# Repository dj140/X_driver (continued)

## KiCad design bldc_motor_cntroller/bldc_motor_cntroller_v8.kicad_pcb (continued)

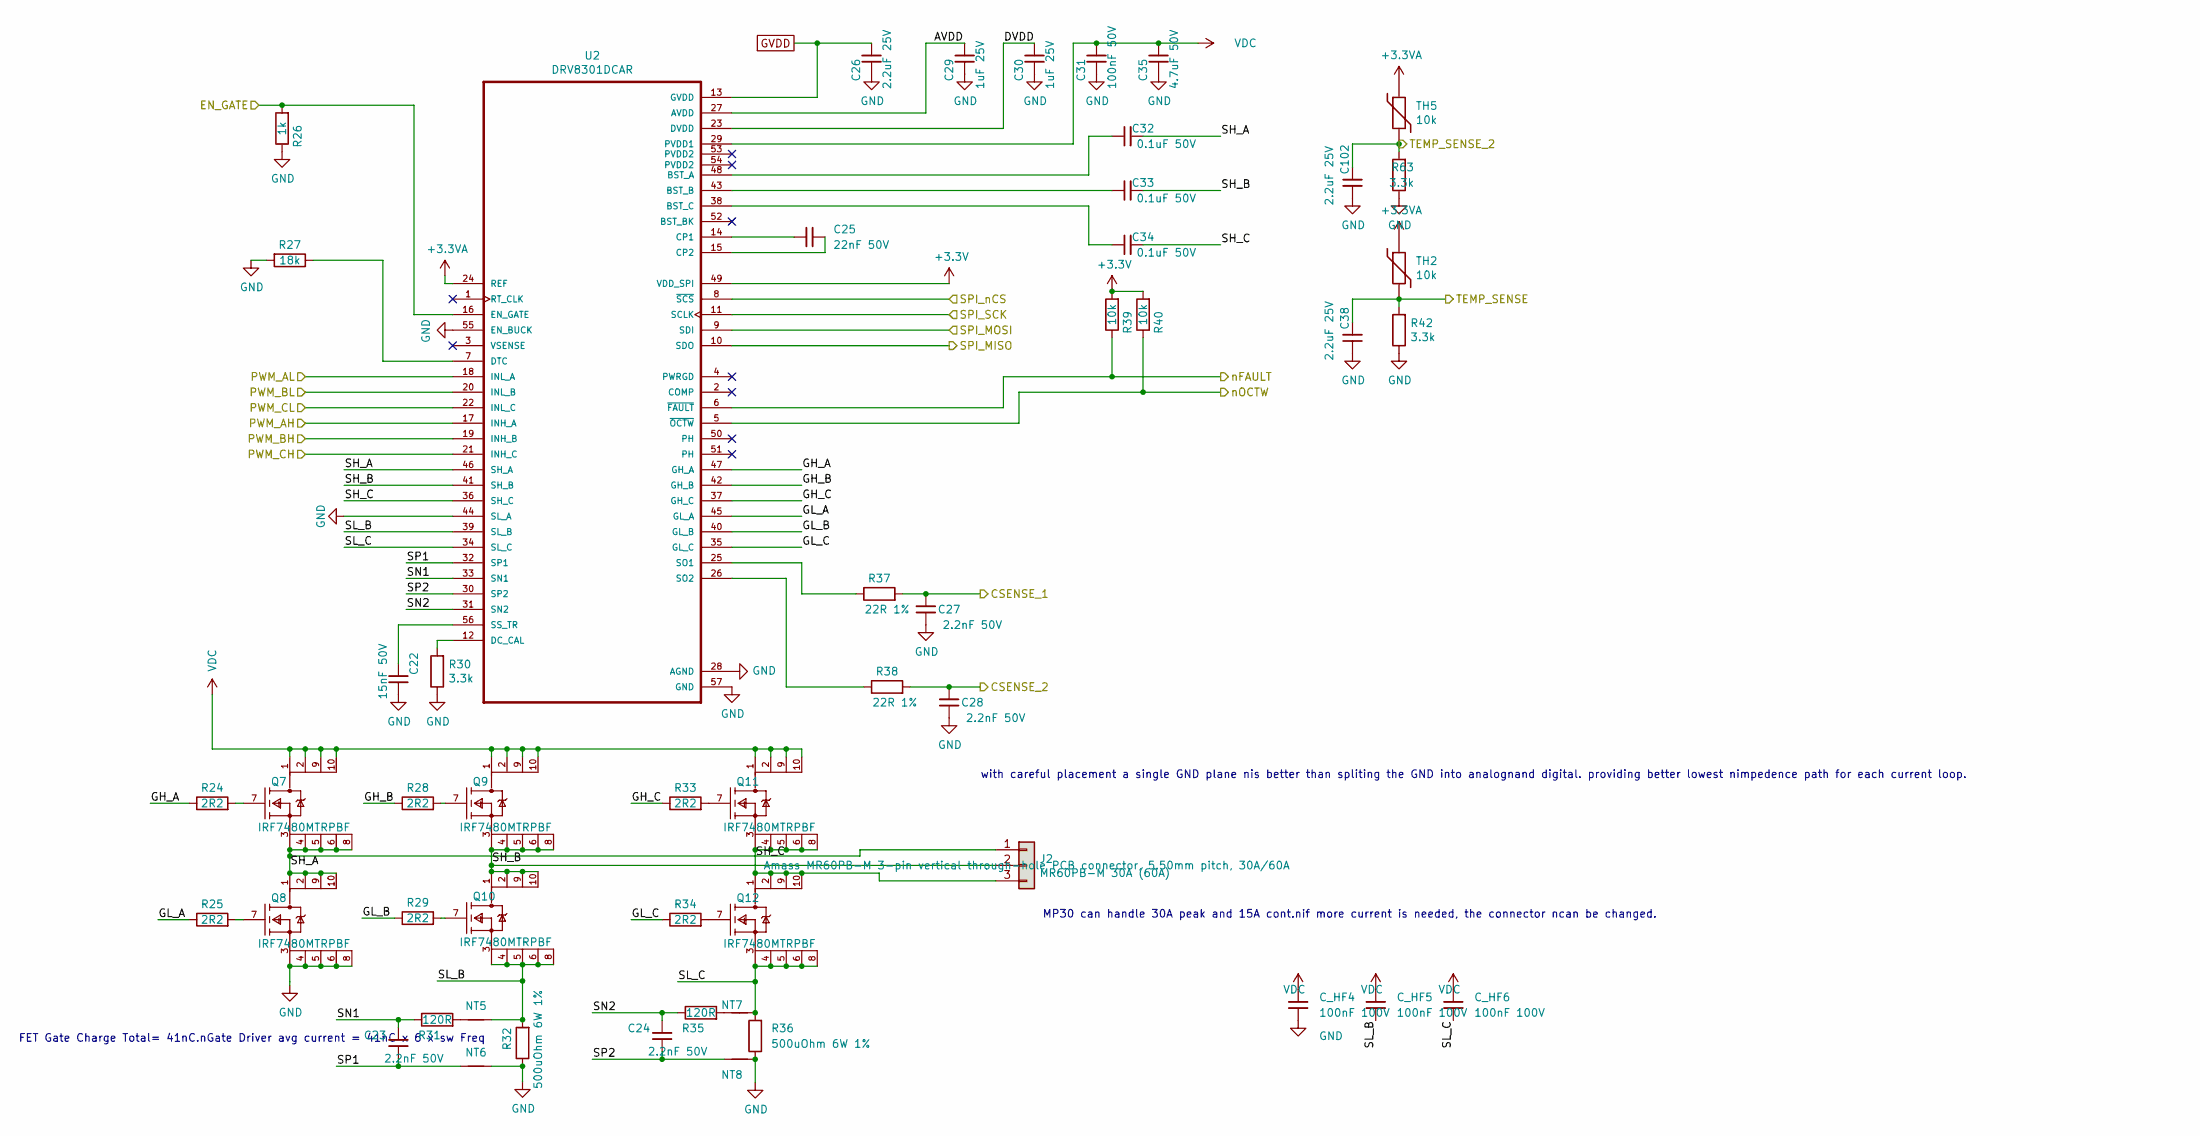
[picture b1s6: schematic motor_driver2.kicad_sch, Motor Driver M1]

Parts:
C22: 15nF 50V; C_0402_1005Metric; MPN GCM155R71E153JA55D
C23, C24, C27, C28: 2.2nF 50V; C_0402_1005Metric; MPN C0402C222J3GEC7411; LCSC Part # C1531
C25: 22nF 50V; C_0402_1005Metric; MPN C0402C223K5REC7411; LCSC Part # C1532
C26, C38, C102: 2.2uF 25V; C_0402_1005Metric; MPN GRM155C81E225KE11D; LCSC Part # C12530
C29, C30: 1uF 25V; C_0402_1005Metric; MPN GMK105CC6105MV-F; LCSC Part # C52923
C31: 100nF 50V; C_0402_1005Metric; MPN GRM155R62A104KE14D
C32, C33, C34: 0.1uF 50V; C_0402_1005Metric; MPN GCM155L8EH104KE07D
C35: 4.7uF 50V; C_1206_3216Metric; MPN HMK325C7475KN-TE
C_HF4, C_HF5, C_HF6: 100nF 100V; C_0603_1608Metric; MPN GCM188R72A104KA64D
J2: MR60PB-M 30A (60A); AMASS_MR60PB-M_1x03_P5.50mm_Vertical; MPN MR60PB-M
NT5, NT6, NT7, NT8: Net-Tie_2; NetTie-2_SMD_Pad0.5mm
Q7, Q8, Q9, Q10, Q11, Q12: IRF7480MTRPBF; Infineon-MG-WDSON-8-05_2016-901-MFG; mouser part number 942-IRF7480MTRPBF; digikey description MOSFET N-CH 40V 217A DIRECTFET
R24, R25, R28, R29, R33, R34: 2R2; R_0402_1005Metric; MPN CRCW04022R20FKEDC
R26: 1k; R_0402_1005Metric; MPN ERJ-2RKF1001X; LCSC Part # C11702
R27: 18k; R_0402_1005Metric; MPN CRCW040218K0FKED; LCSC Part # C25762
R30, R42, R63: 3.3k; R_0402_1005Metric; MPN CRCW04023K30FKEDC; LCSC Part # C25890
R31, R35: 120R; R_0402_1005Metric; MPN ERJ-2RKF1200X; LCSC Part # C25079
R32, R36: 500uOhm 6W 1%; R_2512_6332Metric; MPN CSS2H-2512R-L500F
R37, R38: 22R 1%; R_0402_1005Metric; MPN CRCW040222R0FKEDC; LCSC Part # C25092
R39, R40: 10k; R_0402_1005Metric; MPN CRCW040210K0FKEDC; LCSC Part # C25744
TH2, TH5: 10k; R_0402_1005Metric; MPN CRCW040210K0FKEDC
U2: DRV8301DCAR; DRV8301DCA; MPN DRV8301DCAR

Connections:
+3.3V: R39.2, R40.2, U2.49 (VDD_SPI); also elsewhere on the board
+3.3VA: TH2.1, TH5.1, U2.24 (REF); also elsewhere on the board
/Microcontroller Interface/EN_GATE: R26.2, U2.16 (EN_GATE); also elsewhere on the board
/Microcontroller Interface/M1_AH: U2.17 (INH_A); also elsewhere on the board
/Microcontroller Interface/M1_AL: U2.18 (INL_A); also elsewhere on the board
/Microcontroller Interface/M1_BH: U2.19 (INH_B); also elsewhere on the board
/Microcontroller Interface/M1_BL: U2.20 (INL_B); also elsewhere on the board
/Microcontroller Interface/M1_CH: U2.21 (INH_C); also elsewhere on the board
/Microcontroller Interface/M1_CL: U2.22 (INL_C); also elsewhere on the board
/Microcontroller Interface/M1_SO1: C27.2, R37.2; also elsewhere on the board
/Microcontroller Interface/M1_SO2: C28.2, R38.2; also elsewhere on the board
/Microcontroller Interface/M1_TEMP: C38.1, R42.2, TH2.2; also elsewhere on the board
/Microcontroller Interface/SPI_M1_nCS: U2.8 (~SCS); also elsewhere on the board
/Microcontroller Interface/SPI_MISO: U2.10 (SDO); also elsewhere on the board
/Microcontroller Interface/SPI_MOSI: U2.9 (SDI); also elsewhere on the board
/Microcontroller Interface/SPI_SCK: U2.11 (SCLK); also elsewhere on the board
/Microcontroller Interface/nFAULT: R39.1, U2.6 (~FAULT); also elsewhere on the board
/Motor_Driver2/AVDD: C29.1, U2.27 (AVDD)
/Motor_Driver2/DVDD: C30.1, U2.23 (DVDD)
/Motor_Driver2/GH_A: R24.1, U2.47 (GH_A)
/Motor_Driver2/GH_B: R28.1, U2.42 (GH_B)
/Motor_Driver2/GH_C: R33.1, U2.37 (GH_C)
/Motor_Driver2/GL_A: R25.1, U2.45 (GL_A)
/Motor_Driver2/GL_B: R29.1, U2.40 (GL_B)
/Motor_Driver2/GL_C: R34.1, U2.35 (GL_C)
/Motor_Driver2/SH_A: C32.1, J2.1, Q7.3 (S), Q7.4 (S), Q7.5 (S), Q7.6 (S), Q7.8 (S), Q8.1 (D), Q8.2 (D), Q8.9 (D), Q8.10 (D), U2.46 (SH_A)
/Motor_Driver2/SH_B: C33.1, J2.2, Q9.3 (S), Q9.4 (S), Q9.5 (S), Q9.6 (S), Q9.8 (S), Q10.1 (D), Q10.2 (D), Q10.9 (D), Q10.10 (D), U2.41 (SH_B)
/Motor_Driver2/SH_C: C34.1, J2.3, Q11.3 (S), Q11.4 (S), Q11.5 (S), Q11.6 (S), Q11.8 (S), Q12.1 (D), Q12.2 (D), Q12.9 (D), Q12.10 (D), U2.36 (SH_C)
/Motor_Driver2/SL_B: C_HF5.2, NT5.2, Q10.3 (S), Q10.4 (S), Q10.5 (S), Q10.6 (S), Q10.8 (S), R32.2, U2.39 (SL_B)
/Motor_Driver2/SL_C: C_HF6.2, NT7.2, Q12.3 (S), Q12.4 (S), Q12.5 (S), Q12.6 (S), Q12.8 (S), R36.2, U2.34 (SL_C)
/Motor_Driver2/SN1: C23.2, R31.1, U2.33 (SN1)
/Motor_Driver2/SN2: C24.2, R35.1, U2.31 (SN2)
/Motor_Driver2/SP1: C23.1, NT6.1, U2.32 (SP1)
/Motor_Driver2/SP2: C24.1, NT8.1, U2.30 (SP2)
/Motor_Driver2/TEMP_SENSE_2: C102.1, R63.2, TH5.2
/Motor_Driver2/nOCTW: R40.1, U2.5 (~OCTW)
GND: C22.1, C26.2, C27.1, C28.1, C29.2, C30.2, C31.2, C35.2, C38.2, C102.2, C_HF4.2, NT6.2, NT8.2, Q8.3 (S), Q8.4 (S), Q8.5 (S), Q8.6 (S), Q8.8 (S), R26.1, R27.2, R30.1, R32.1, R36.1, R42.1, R63.1, U2.28 (AGND), U2.44 (SL_A), U2.55 (EN_BUCK), U2.57 (GND), U2.V; also elsewhere on the board
GVDD: C26.1, U2.13 (GVDD); also elsewhere on the board
unnamed: NT5.1, R31.2
unnamed: NT7.1, R35.2
unnamed: Q7.7 (G), R24.2
unnamed: Q8.7 (G), R25.2
unnamed: Q9.7 (G), R28.2
unnamed: Q10.7 (G), R29.2
unnamed: Q11.7 (G), R33.2
unnamed: Q12.7 (G), R34.2
unnamed: C32.2, U2.48 (BST_A)
unnamed: C33.2, U2.43 (BST_B)
unnamed: C34.2, U2.38 (BST_C)
unnamed: C25.1, U2.14 (CP1)
unnamed: C25.2, U2.15 (CP2)
unnamed: R30.2, U2.12 (DC_CAL)
unnamed: R27.1, U2.7 (DTC)
unnamed: R37.1, U2.25 (SO1)
unnamed: R38.1, U2.26 (SO2)
unnamed: C22.2, U2.56 (SS_TR)
VDC: C31.1, C35.1, C_HF4.1, C_HF5.1, C_HF6.1, Q7.1 (D), Q7.2 (D), Q7.9 (D), Q7.10 (D), Q9.1 (D), Q9.2 (D), Q9.9 (D), Q9.10 (D), Q11.1 (D), Q11.2 (D), Q11.9 (D), Q11.10 (D), U2.29 (PVDD1); also elsewhere on the board

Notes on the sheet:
FET Gate Charge Total= 41nC.nGate Driver avg current = 41nC x 6 x sw Freq
MP30 can handle 30A peak and 15A cont.nif more current is needed, the connector ncan be changed.
with careful placement a single GND plane nis better than spliting the GND into analognand digital. providing better lowest nimpedence path for each current loop.

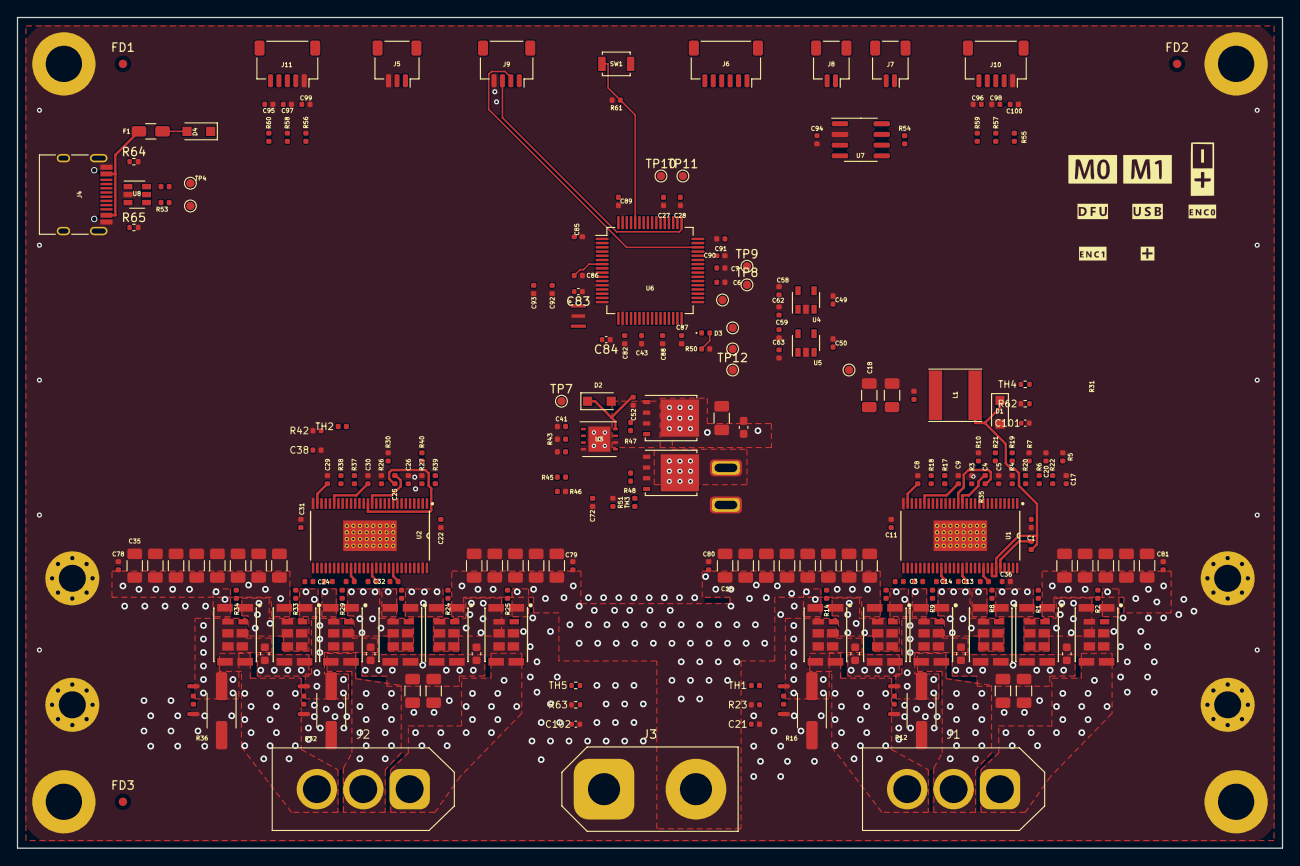
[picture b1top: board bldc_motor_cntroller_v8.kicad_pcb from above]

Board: 4 copper layers, 150.0 x 98.5 mm, 250 parts (0 on the bottom side), 157 nets.

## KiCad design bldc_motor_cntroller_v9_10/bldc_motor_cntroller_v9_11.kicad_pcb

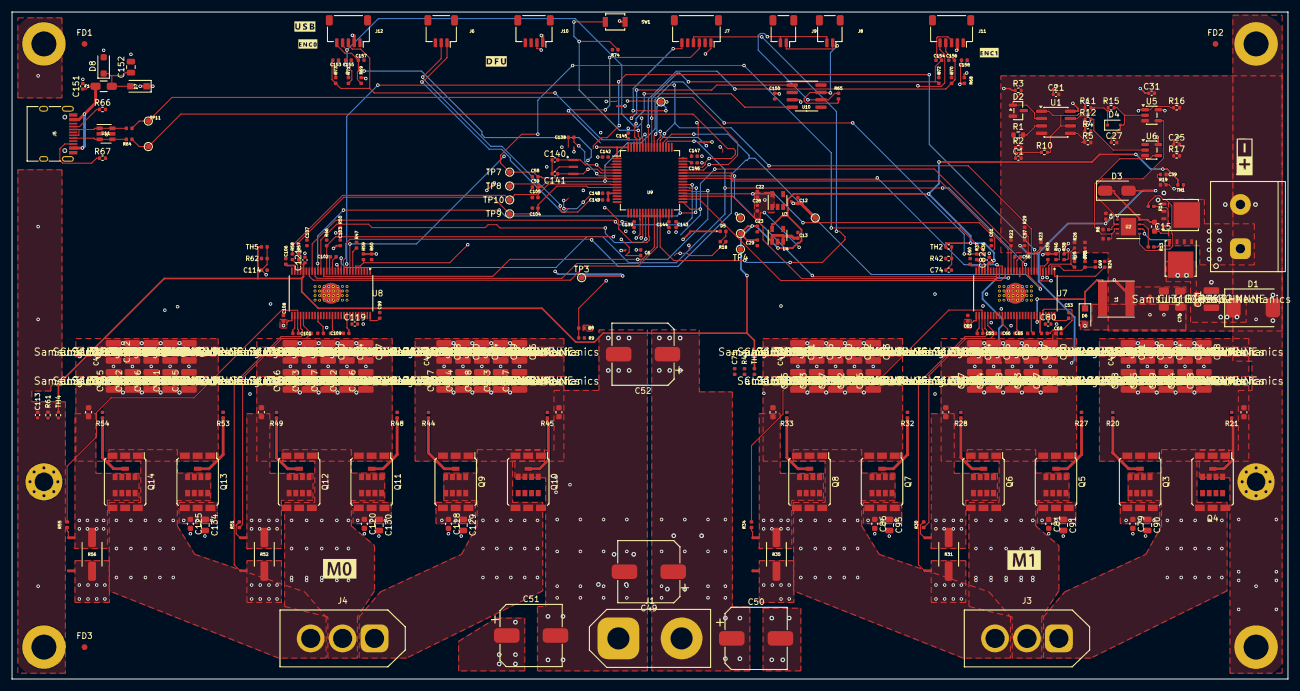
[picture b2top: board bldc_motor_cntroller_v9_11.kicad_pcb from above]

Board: 4 copper layers, 220.0 x 115.0 mm, 329 parts (0 on the bottom side), 165 nets.

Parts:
C1: 100pF 50V; C_0402_1005Metric
C2, C3, C5, C7, C8, C9, C10, C11, C14, C16, C17, C18, C19, C20, C24, C26, C30, C32, C33, C34, C35, C36, C37, C38, C40, C41, C42, C43, C44, C71, C76, C77, C78, C83, C84, C85, C87, C88, C89, C92, C93, C94, C96, C97, C98, C112, C115, C116, C117, C122, C123, C124, C126, C127, C128, C131, C132, C133, C135, C136, C137: 4.7uF 100V; C_1210_3225Metric
C4, C57, C74, C75, C103, C113, C114: 2.2uF 25V; C_0402_1005Metric
C6, C73: 270pF 50V; C_0402_1005Metric
C12, C13, C22, C23, C60, C61, C72, C106, C107, C149: 1uF 25V; C_0402_1005Metric
C15: 470nF 50V; C_0603_1608Metric
C21, C25, C31, C138: 100nF 16V; C_0402_1005Metric
C27: 470pF 50V; C_0402_1005Metric
C28, C29: 0.1uF 16V; C_0402_1005Metric
C39, C144, C146: 2.2uF 16V; C_0402_1005Metric
C45, C46, C47, C48, C62, C63, C65, C66, C67, C68, C80, C82, C108, C119, C121, C151: 100nF 50V; C_0402_1005Metric
C49, C50, C51, C52: 100uF 100V; CP_Elec_10x10.5
C53, C99: 15nF 50V; C_0402_1005Metric
C54, C55, C58, C59, C100, C101, C104, C105: 2.2nF 50V; C_0402_1005Metric
C56, C102: 22nF 50V; C_0402_1005Metric
C64, C70: 47uF 16V; C_1206_3216Metric
C69: 82pF 50V; C_0402_1005Metric
C79, C81, C86, C118, C120, C125: 100nF 100V; C_0603_1608Metric
C90, C91, C95, C129, C130, C134: 1uF 100V; C_0805_2012Metric
C109, C110, C111: 0.1uF 50V; C_0402_1005Metric
C139, C142, C143, C145, C147, C148, C150, C153, C154, C155, C156, C157, C158: 100nF; C_0402_1005Metric
C140, C141: 12pF; C_0402_1005Metric
C152: 4.7uF 25V; C_0805_2012Metric
C_AUX1: 100nF 100V; C_0603_1608Metric
C_HF1, C_HF2, C_HF3, C_HF4, C_HF5, C_HF6: 100nF 100V; C_0603_1608Metric
D1: 5.0SMDJ48A; D_SMC
D2: LM4040C25IDBZR; SOT-23
D3: STPS1H100A; D_SMA
D4: BAT54J; D_SOD-323F
D5: GREEN; LED_0402_1005Metric
D6, D7: MBR2H100SFT3G; D_SOD-123F
D8: SMF5.0A; D_SOD-123F
F1: Fuse_500MA; Fuse_1206_3216Metric
FD1, FD2, FD3: Fiducial; Fiducial_1mm_Mask2mm
G1: LOGO; M00
G2: LOGO; M1
G3: LOGO; batt
G4: LOGO; DFU
G5: LOGO; USB
G6: LOGO; ENC0
G7: LOGO; ENC1
H1, H4: MountingHole_3.2mm_M3_Pad_Via
H2, H3, H5, H6: MountingHole_Pad; MountingHole_4.3mm_M4_Pad
J1: XT90; AMASS_XT90-M_1x02_P10.90mm_Vertical
J2: DB910-7.62-2P-GN-S; DORABO_DB910-7.62-2P
J3, J4: MR60PB-M 30A (60A); AMASS_MR60PB-M_1x03_P5.50mm_Vertical
J5: USB_C_Receptacle_USB2.0; USB_C_Receptacle_HRO_TYPE-C-31-M-12
J6: Conn_01x03; JST_SH_SM03B-SRSS-TB_1x03-1MP_P1.00mm_Horizontal
J7: Conn_01x06; JST_SH_SM06B-SRSS-TB_1x06-1MP_P1.00mm_Horizontal
J8, J9: Conn_01x02; JST_SH_SM02B-SRSS-TB_1x02-1MP_P1.00mm_Horizontal
J10: Conn_01x04; JST_SH_SM04B-SRSS-TB_1x04-1MP_P1.00mm_Horizontal
J11, J12: Conn_01x05; JST_SH_SM05B-SRSS-TB_1x05-1MP_P1.00mm_Horizontal
L1: 33uH 1.4A; L_Taiyo-Yuden_NR-60xx
NT1, NT2, NT3, NT4, NT5, NT6, NT7, NT8: Net-Tie_2; NetTie-2_SMD_Pad0.5mm
Q1, Q2: CSD18540Q5B; TDSON-8-1
Q3, Q4, Q5, Q6, Q7, Q8, Q9, Q10, Q11, Q12, Q13, Q14: IRF7759L2TRPBF; DirectFET_L8
R1: 180k; R_0603_1608Metric
R2, R4, R5, R38, R39, R40, R59, R60, R74: 10k; R_0402_1005Metric
R3, R9, R15, R18, R22, R46: 1k; R_0402_1005Metric
R6, R7, R19, R26, R29, R42, R43, R50, R61, R62, R68, R69, R70, R71, R72, R73: 3.3k; R_0402_1005Metric
R8, R23, R25, R47: 18k; R_0402_1005Metric
R10: 330k; R_0402_1005Metric
R11, R12: 4.7k; R_0402_1005Metric
R13, R14, R20, R21, R27, R28, R32, R33, R44, R45, R48, R49, R53, R54: 2R2; R_0402_1005Metric
R16, R17: 100k; R_0402_1005Metric
R24: 220k 1%; R_0402_1005Metric
R30, R34, R51, R55, R65: 120R; R_0402_1005Metric
R31, R35, R52, R56: 500uOhm 6W 1%; R_2512_6332Metric
R36, R37, R57, R58, R63, R64: 22R 1%; R_0402_1005Metric
R41: 47k 1%; R_0402_1005Metric
R66, R67: 5.1k 1%; R_0402_1005Metric
SW1: B3U-1000P-B; SW_SPST_B3U-1000P
TH1, TH2, TH3, TH4, TH5: 10k; R_0402_1005Metric
TP1, TP2, TP3, TP4, TP5, TP6, TP7, TP8, TP9, TP10, TP11, TP12: TestPoint; TestPoint_Pad_D1.0mm
U1: LM393BIDR; SOIC-8_3.9x4.9mm_P1.27mm
U2: LM5109BSD; WSON-8_4x4mm_P0.8mm
U3: SPX3819M5-L-3-3; SOT-23-5
U4: LP5907MFX-3.3; SOT-23-5
U5: SN74LVC1G32DBVR; SOT-23-5
U6: SN74LVC1G08DBVR; SOT-23-5
U7, U8: DRV8301DCAR; DRV8301DCA_v9
U9: STM32F405RGTx; LQFP-64_10x10mm_P0.5mm
U10: SN65HVD232; SOIC-8_3.9x4.9mm_P1.27mm
U11: USBLC6-2SC6; SOT-23-6
Y1: CSTCE8M00G55-R0

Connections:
+3.3V: C21.1, C22.1, C25.1, C28.1, C31.1, C80.1, C119.1, C139.1, C142.1, C143.1, C145.1, C147.1, C150.2, D5.1, R3.1, R4.1, R11.1, R12.1, R38.2, R39.2, R40.2, R59.2, R60.2, R68.1, R69.1, R70.1, R71.1, R72.1, R73.1, SW1.1, TP1.1, U1.8, U3.5, U5.5, U6.5, U7.49, U8.49, U9.1, U9.19, U9.32, U9.48, U9.64, U10.3
+3.3VA: C23.1, C29.1, C82.1, C121.1, C148.1, C149.1, TH1.1, TH2.1, TH3.1, TH4.1, TH5.1, TP2.1, U4.5, U7.24, U8.24, U9.13
+5V: C12.1, C13.1, C64.1, C70.1, C72.1, D7.1, J10.1, J11.2, J12.2, L1.2, R25.2, TP5.1, U3.1, U3.3, U4.1, U4.3, U11.5
/I/O Interface/BOOT0: R74.2, SW1.2, U9.60
/I/O Interface/CAN_D: U9.62, U10.1
/I/O Interface/CAN_R: U9.61, U10.4
/I/O Interface/DEBUG_SWCLK: J10.3, U9.49
/I/O Interface/DEBUG_SWDIO: J10.2, U9.46
/I/O Interface/ENC0_A: C154.2, J11.3, R72.2, U9.56
/I/O Interface/ENC0_B: C156.2, J11.4, R70.2, U9.57
/I/O Interface/ENC0_Z: C158.2, J11.5, R68.2, U9.40
/I/O Interface/ENC1_A: C153.2, J12.3, R73.2, U9.58
/I/O Interface/ENC1_B: C155.2, J12.4, R71.2, U9.59
/I/O Interface/ENC1_Z: C157.2, J12.5, R69.2, U9.4
/I/O Interface/GPIO_1: J6.1, U9.14
/I/O Interface/GPIO_2: J6.2, U9.15
/I/O Interface/GPIO_3: J7.1, U9.16
/I/O Interface/GPIO_4: J7.2, U9.17
/I/O Interface/GPIO_5: J7.3, U9.24
/I/O Interface/GPIO_6: J7.4, U9.28
/I/O Interface/GPIO_7: J7.5, U9.50
/I/O Interface/GPIO_8: J7.6, U9.55
/I/O Interface/USB_CC1: J5.A5, R66.1
/I/O Interface/USB_CC2: J5.B5, R67.1
/I/O Interface/USB_DN: R63.1, TP11.1, U9.44
/I/O Interface/USB_DP: R64.1, TP12.1, U9.45
/I/O Interface/USB_J4_DN: J5.A7, J5.B7, R63.2, U11.1, U11.6
/I/O Interface/USB_J4_DP: J5.A6, J5.B6, R64.2, U11.3, U11.4
/I/O Interface/USB_VBUS_PROT: C152.1, D7.2, D8.1, F1.2
/I/O Interface/USB_VBUS_RAW: C151.1, F1.1, J5.A4, J5.A9, J5.B4, J5.B9
/Microcontroller Interface/AUX_TEMP: C39.1, R19.2, TH1.2, U9.21
/Microcontroller Interface/EN_GATE: R22.2, R46.2, U7.16, U8.16, U9.33
/Microcontroller Interface/M0_AH: U7.17, U9.41
/Microcontroller Interface/M0_AL: U7.18, U9.34
/Microcontroller Interface/M0_BH: U7.19, U9.42
/Microcontroller Interface/M0_BL: U7.20, U9.35
/Microcontroller Interface/M0_CH: U7.21, U9.43
/Microcontroller Interface/M0_CL: U7.22, U9.36
/Microcontroller Interface/M0_SO1: C58.2, R36.2, TP7.1, U9.8
/Microcontroller Interface/M0_SO2: C59.2, R37.2, TP8.1, U9.9
/Microcontroller Interface/M0_TEMP: C75.1, R43.2, TH3.2, U9.25
/Microcontroller Interface/M1_AH: U8.17, U9.37
/Microcontroller Interface/M1_AL: U8.18, U9.23
/Microcontroller Interface/M1_BH: U8.19, U9.38
/Microcontroller Interface/M1_BL: U8.20, U9.26
/Microcontroller Interface/M1_CH: U8.21, U9.39
/Microcontroller Interface/M1_CL: U8.22, U9.27
/Microcontroller Interface/M1_SO1: C104.2, R57.2, TP9.1, U9.11
/Microcontroller Interface/M1_SO2: C105.2, R58.2, TP10.1, U9.10
/Microcontroller Interface/M1_TEMP: C114.1, R62.2, TH5.2, U9.20
/Microcontroller Interface/SPI_M0_nCS: U7.8, U9.2
/Microcontroller Interface/SPI_M1_nCS: U8.8, U9.3
/Microcontroller Interface/SPI_MISO: U7.10, U8.10, U9.52
/Microcontroller Interface/SPI_MOSI: U7.9, U8.9, U9.53
/Microcontroller Interface/SPI_SCK: U7.11, U8.11, U9.51
/Microcontroller Interface/VBUS_S: C6.1, R8.2, R9.1, U9.22
/Microcontroller Interface/nFAULT: R39.1, R59.1, TP6.1, U7.6, U8.6, U9.54
/Motor Driver/AVDD: C60.1, U7.27
/Motor Driver/DVDD: C61.1, U7.23
/Motor Driver/GH_A: R20.1, U7.47
/Motor Driver/GH_B: R27.1, U7.42
/Motor Driver/GH_C: R32.1, U7.37
/Motor Driver/GL_A: R21.1, U7.45
/Motor Driver/GL_B: R28.1, U7.40
/Motor Driver/GL_C: R33.1, U7.35
/Motor Driver/PWRGD: R38.1, U7.4
/Motor Driver/SH_A: C65.1, J3.1, Q3.3, Q4.1, U7.46
/Motor Driver/SH_B: C66.1, J3.2, Q5.3, Q6.1, U7.41
/Motor Driver/SH_C: C67.1, J3.3, Q7.3, Q8.1, U7.36
/Motor Driver/SL_B: C_HF2.2, NT1.2, Q6.3, R31.2, U7.39
/Motor Driver/SL_C: C_HF3.2, NT3.2, Q8.3, R35.2, U7.34
/Motor Driver/SN1: C54.2, R30.1, U7.33
/Motor Driver/SN2: C55.2, R34.1, U7.31
/Motor Driver/SP1: C54.1, NT2.1, U7.32
/Motor Driver/SP2: C55.1, NT4.1, U7.30
/Motor Driver/TEMP_SENSE_2: C74.1, R42.2, TH2.2
/Motor Driver/nOCTW: R40.1, U7.5
/Motor_Driver2/AVDD: C106.1, U8.27
/Motor_Driver2/DVDD: C107.1, U8.23
/Motor_Driver2/GH_A: R44.1, U8.47
/Motor_Driver2/GH_B: R48.1, U8.42
/Motor_Driver2/GH_C: R53.1, U8.37
/Motor_Driver2/GL_A: R45.1, U8.45
/Motor_Driver2/GL_B: R49.1, U8.40
/Motor_Driver2/GL_C: R54.1, U8.35
/Motor_Driver2/SH_A: C109.1, J4.1, Q9.3, Q10.1, U8.46
/Motor_Driver2/SH_B: C110.1, J4.2, Q11.3, Q12.1, U8.41
/Motor_Driver2/SH_C: C111.1, J4.3, Q13.3, Q14.1, U8.36
/Motor_Driver2/SL_B: C_HF5.2, NT5.2, Q12.3, R52.2, U8.39
/Motor_Driver2/SL_C: C_HF6.2, NT7.2, Q14.3, R56.2, U8.34
/Motor_Driver2/SN1: C100.2, R51.1, U8.33
/Motor_Driver2/SN2: C101.2, R55.1, U8.31
/Motor_Driver2/SP1: C100.1, NT6.1, U8.32
/Motor_Driver2/SP2: C101.1, NT8.1, U8.30
/Motor_Driver2/TEMP_SENSE_2: C113.1, R61.2, TH4.2
/Motor_Driver2/nOCTW: R60.1, U8.5
/Power Management/HS: C15.2, J2.1, Q1.1, Q1.2, Q1.3, Q2.5, U2.6
/Power Management/OVP_ACTIVE: D4.1, R10.2, R11.2, R15.1, U1.1, U1.6
/Power Management/OVP_ACTIVE_DLY: C27.1, D4.2, R15.2, U5.2
/Power Management/OVP_VMID: R4.2, R5.1, U1.5
/Power Management/OVP_VREF: D2.1, R3.2, U1.2
/Power Management/OVP_VSENSE: C1.1, R1.2, R2.1, R10.1, U1.3
/Power Management/nOVP_ACTIVE: R12.2, U1.7, U6.2
CAN_H: J8.1, J9.1, R65.2, U10.7
CAN_L: J8.2, J9.2, R65.1, U10.6
GND: C1.2, C2.2, C3.2, C4.2, C5.2, C6.2, C7.2, C8.2, C9.2, C10.2, C11.2, C12.2, C13.2, C14.2, C16.2, C17.2, C18.2, C19.2, C20.2, C21.2, C22.2, C23.2, C24.2, C25.2, C26.2, C27.2, C28.2, C29.2, C30.2, C31.2, C32.2, C33.2, C34.2, C35.2, C36.2, C37.2, C38.2, C39.2, C40.2, C41.2, C42.2, C43.2, C44.2, C45.2, C46.2, C47.2, C48.2, C49.2, C50.2, C51.2, C52.2, C53.1, C57.2, C58.1, C59.1, C60.2, C61.2, C63.2, C64.2, C68.2, C69.2, C70.2, C71.2, C72.2, C73.2, C74.2, C75.2, C76.2, C77.2, C78.2, C79.2, C80.2, C81.2, C82.2, C83.2, C84.2, C85.2, C86.2, C87.2, C88.2, C89.2, C90.2, C91.2, C92.2, C93.2, C94.2, C95.2, C96.2, C97.2, C98.2, C99.1, C103.2, C104.1, C105.1, C106.2, C107.2, C108.2, C112.2, C113.2, C114.2, C115.2, C116.2, C117.2, C118.2, C119.2, C120.2, C121.2, C122.2, C123.2, C124.2, C125.2, C126.2, C127.2, C128.2, C129.2, C130.2, C131.2, C132.2, C133.2, C134.2, C135.2, C136.2, C137.2, C138.2, C139.2, C140.1, C141.1, C142.2, C143.2, C144.2, C145.2, C146.2, C147.2, C148.2, C149.2, C150.1, C151.2, C152.2, C153.1, C154.1, C155.1, C156.1, C157.1, C158.1, C_AUX1.2, C_HF1.2, C_HF4.2, D1.2, D2.2, D6.2, D8.2, H1.1 (1_1), H2.1 (1_1), H3.1 (1_1), H4.1 (1_1), H5.1 (1_1), H6.1 (1_1), J1.1, J2.2, J5.A1, J5.A12, J5.B1, J5.B12, J5.S1, J6.3, J10.4, J11.1, J12.1, NT2.2, NT4.2, NT6.2, NT8.2, Q2.1, Q2.2, Q2.3, Q4.3, Q10.3, R2.2, R5.2, R6.1, R7.1, R9.2, R16.2, R17.2, R18.2, R19.1, R22.1, R23.2, R24.2, R26.1, R29.1, R31.1, R35.1, R42.1, R43.1, R46.1, R47.2, R50.1, R52.1, R56.1, R61.1, R62.1, R66.2, R67.2, R74.1, TP4.1, U1.4, U2.4, U2.9, U3.2, U4.2, U5.3, U6.3, U7.28, U7.44, U7.57, U8.28, U8.44, U8.55, U8.57, U9.12, U9.18, U9.63, U10.2, U11.2, Y1.3
GVDD: C4.1, C57.1, C103.1, D3.2, TP3.1, U2.1, U7.13, U8.13
unnamed: C73.1, R41.2
unnamed: C15.1, D3.1, U2.8
unnamed: D5.2, R18.1
unnamed: C62.1, D6.1, L1.1, U7.50, U7.51
unnamed: NT1.1, R30.2
unnamed: NT3.1, R34.2
unnamed: NT5.1, R51.2
unnamed: NT7.1, R55.2
unnamed: Q1.4, R13.1
unnamed: Q2.4, R14.1
unnamed: Q3.2, R20.2
unnamed: Q4.2, R21.2
unnamed: Q5.2, R27.2
unnamed: Q6.2, R28.2
unnamed: Q7.2, R32.2
unnamed: Q8.2, R33.2
unnamed: Q9.2, R44.2
unnamed: Q10.2, R45.2
unnamed: Q11.2, R48.2
unnamed: Q12.2, R49.2
unnamed: Q13.2, R53.2
unnamed: Q14.2, R54.2
unnamed: R13.2, U2.7
unnamed: R14.2, U2.5
unnamed: C65.2, U7.48
unnamed: C66.2, U7.43
unnamed: C62.2, U7.52
unnamed: C67.2, U7.38
unnamed: C69.1, R41.1, U7.2
unnamed: C56.1, U7.14
unnamed: C56.2, U7.15
unnamed: R29.2, U7.12
unnamed: R23.1, U7.7
unnamed: R24.1, U7.1
unnamed: R36.1, U7.25
unnamed: R37.1, U7.26
unnamed: C53.2, U7.56
unnamed: R25.1, R26.2, U7.3
unnamed: C109.2, U8.48
unnamed: C110.2, U8.43
unnamed: C111.2, U8.38
unnamed: C102.1, U8.14
unnamed: C102.2, U8.15
unnamed: R50.2, U8.12
unnamed: R47.1, U8.7
unnamed: R57.1, U8.25
unnamed: R58.1, U8.26
unnamed: C99.2, U8.56
unnamed: C138.1, U9.7
unnamed: C140.2, U9.5, Y1.1
unnamed: C141.2, U9.6, Y1.2
unnamed: C144.1, U9.31
unnamed: C146.1, U9.47
OVP_IN_HI: R16.1, U5.1, U9.30
OVP_IN_LI: R17.1, U6.1, U9.29
U3_HI_DRV: R6.2, U2.2, U5.4
U3_LI_DRV: R7.2, U2.3, U6.4
VDC: C2.1, C3.1, C5.1, C7.1, C8.1, C9.1, C10.1, C11.1, C14.1, C16.1, C17.1, C18.1, C19.1, C20.1, C24.1, C26.1, C30.1, C32.1, C33.1, C34.1, C35.1, C36.1, C37.1, C38.1, C40.1, C41.1, C42.1, C43.1, C44.1, C45.1, C46.1, C47.1, C48.1, C49.1, C50.1, C51.1, C52.1, C63.1, C68.1, C71.1, C76.1, C77.1, C78.1, C79.1, C81.1, C83.1, C84.1, C85.1, C86.1, C87.1, C88.1, C89.1, C90.1, C91.1, C92.1, C93.1, C94.1, C95.1, C96.1, C97.1, C98.1, C108.1, C112.1, C115.1, C116.1, C117.1, C118.1, C120.1, C122.1, C123.1, C124.1, C125.1, C126.1, C127.1, C128.1, C129.1, C130.1, C131.1, C132.1, C133.1, C134.1, C135.1, C136.1, C137.1, C_AUX1.1, C_HF1.1, C_HF2.1, C_HF3.1, C_HF4.1, C_HF5.1, C_HF6.1, D1.1, J1.2, Q1.5, Q3.1, Q5.1, Q7.1, Q9.1, Q11.1, Q13.1, R1.1, R8.1, U7.29, U7.53, U7.54, U8.29
